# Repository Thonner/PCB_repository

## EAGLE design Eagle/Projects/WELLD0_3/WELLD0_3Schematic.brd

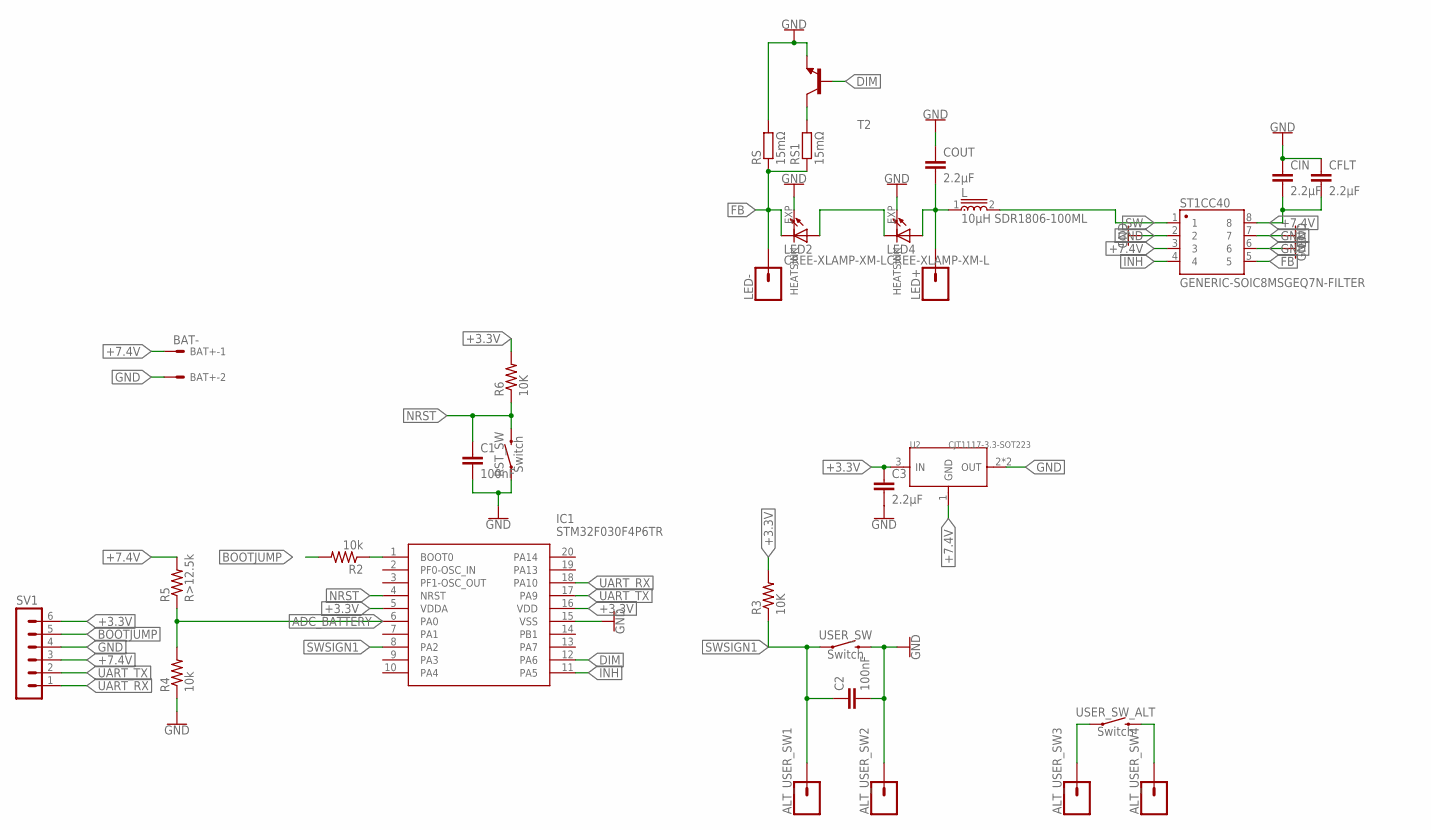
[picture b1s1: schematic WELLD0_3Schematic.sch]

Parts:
ALT_USER_SW1, ALT_USER_SW2, ALT_USER_SW3, ALT_USER_SW4: CONN_01; 1X01
BAT+: BAT-; 6410-02
C1, C2: 100nF; C0603
C3: 2.2µF; C0603
CFLT: 2.2µF; C0603
CIN: 2.2µF; C0603
COUT: 2.2µF; C0603
IC1: STM32F030F4P6TR; SOP65P640X120-20N
L: 10µH SDR1806-100ML; INDP1830X1400X690L250X260N
LED2, LED4: CREE-XLAMP-XM-L
LED+: CONN_01; 1X01
LED-: CONN_01; 1X01
R2, R4: 10k; R0603
R3, R6: 10K; R0603
R5: R>12.5k; R0603
RS, RS1: 15mΩ; M1206
RST_SW: Switch; TACTILE_SWITCH_SMD_6.2MM_TALL
ST1CC40: GENERIC-SOIC8MSGEQ7N-FILTER; SO08
SV1: MA06-1
T2: -NPN-SOT23-BEC; SOT23-BEC
U2: CJT1117-3.3-SOT223; SOT-223
USER_SW: Switch; TACTILE_SWITCH_SMD_6.2MM_TALL
USER_SW_ALT: Switch; TACTILE_SWITCH_SMD_6.2MM_TALL

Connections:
+3.3V: C3.1, IC1.5 (VDDA), IC1.16 (VDD), R3.2, R6.2, SV1.6, U2.3 (IN)
+7.4V: BAT+.1, CFLT.2, CIN.2, R5.2, ST1CC40.3, ST1CC40.8, SV1.3, U2.1 (GND)
ADC_BATTERY: IC1.6 (PA0), R4.2, R5.1
BOOTJUMP: R2.2, SV1.5
DIM: IC1.12 (PA6), T2.B
FB: LED2.C, LED2.C@1 (C), LED-.1, RS.1, RS1.1, ST1CC40.5
GND: ALT_USER_SW2.1, BAT+.2, C1.2, C2.2, C3.2, CFLT.1, CIN.1, COUT.1, IC1.15 (VSS), LED2.EXP (HEATSINK), LED4.EXP (HEATSINK), R4.1, RS.2, RST_SW.A2 (1), ST1CC40.2, ST1CC40.6, ST1CC40.7, SV1.4, T2.E, U2.2 (OUT), U2.TER (OUT), USER_SW.B2 (2)
INH: IC1.11 (PA5), ST1CC40.4
unnamed: COUT.2, L.1, LED4.A, LED4.A@1 (A), LED+.1
unnamed: LED2.A, LED2.A@1 (A), LED4.C, LED4.C@1 (C)
unnamed: RS1.2, T2.C
unnamed: ALT_USER_SW3.1, USER_SW_ALT.A2 (1)
unnamed: ALT_USER_SW4.1, USER_SW_ALT.B2 (2)
unnamed: IC1.1 (BOOT0), R2.1
NRST: C1.1, IC1.4 (NRST), R6.1, RST_SW.B2 (2)
SW: L.2, ST1CC40.1
SWSIGN1: ALT_USER_SW1.1, C2.1, IC1.8 (PA2), R3.1, USER_SW.A2 (1)
UART_RX: IC1.18 (PA10), SV1.1
UART_TX: IC1.17 (PA9), SV1.2

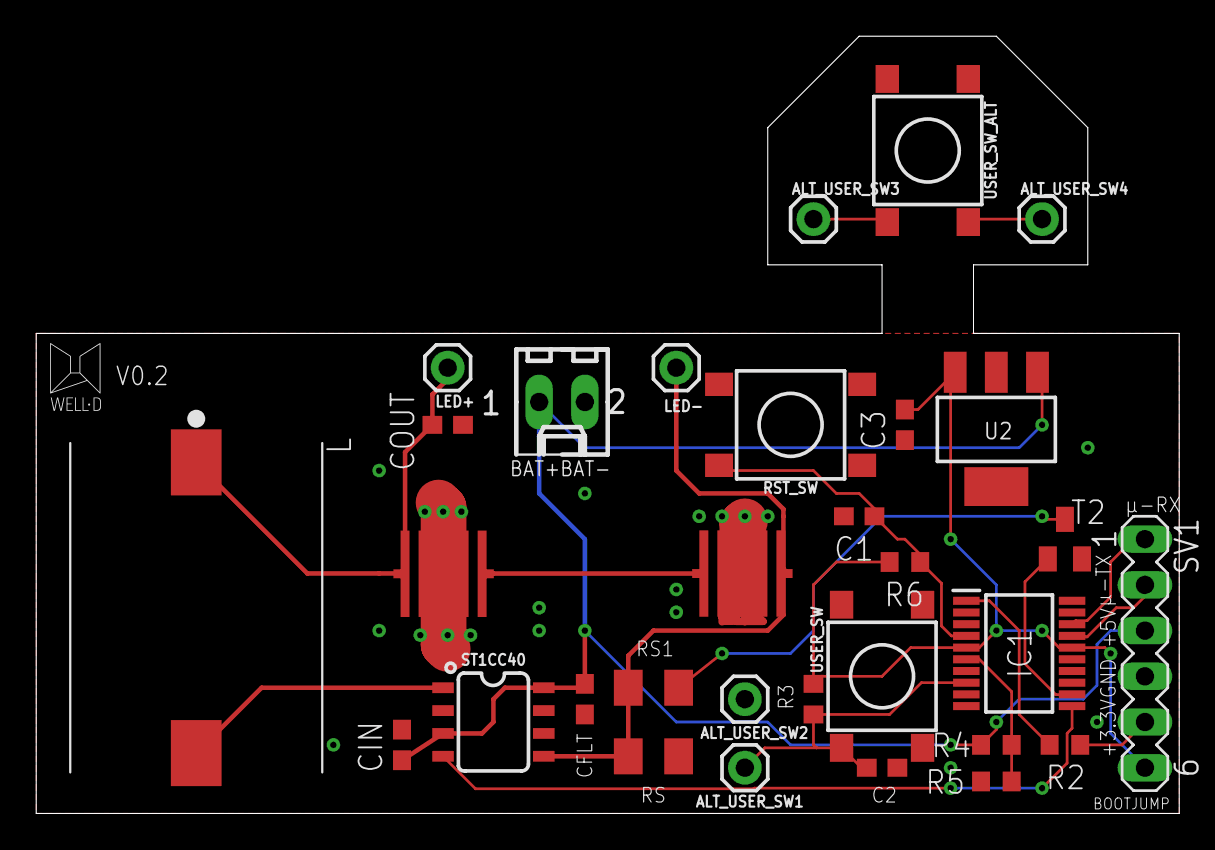
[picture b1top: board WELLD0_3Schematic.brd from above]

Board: 2 copper layers, 63.5 x 43.2 mm, 31 parts (0 on the bottom side), 19 nets.

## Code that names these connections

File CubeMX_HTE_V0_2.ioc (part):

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Mcu.Name=STM32F030F4Px
Mcu.Package=TSSOP20
Mcu.UserName=STM32F030F4Px
PA0.GPIOParameters=GPIO_Label
PA0.GPIO_Label=ADC_battery_mon
PA0.Mode=IN0
PA0.Signal=ADC_IN0
PA10.GPIOParameters=GPIO_Label
PA10.GPIO_Label=UART_RX_PROG
PA10.Mode=Asynchronous
PA10.Signal=USART1_RX
PA2.GPIOParameters=GPIO_PuPd,GPIO_Label
PA2.GPIO_Label=User_Input
PA2.GPIO_PuPd=GPIO_PULLUP
PA2.Signal=GPIO_Input
PA5.GPIOParameters=GPIO_Label
PA5.GPIO_Label=Driver_OnOff_out
PA5.Signal=GPIO_Output
PA6.GPIOParameters=GPIO_Label
PA6.GPIO_Label=DIM_Trans_Out
PA6.Signal=GPIO_Output
PA9.GPIOParameters=GPIO_Label
PA9.GPIO_Label=UART_TX_PROG
PA9.Mode=Asynchronous
PA9.Signal=USART1_TX
board=custom

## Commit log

2018-10-09 Basic component library
2018-10-09 Started eagle project
2018-10-09 More libraries
2018-10-09 Barely started schematic
2018-10-10 Here goes libraries
2018-10-10 LED driver circuit made. (Almost) Have not considered supply, or turn off signal or the dimming mechanism
2018-10-16 Libraries
2018-10-16 Work from 16/10-18
2018-10-24 Circuit done - i guess 24/10-18
2018-10-25 Ready for final thoughts
2018-10-26 Final form - missing heatsink
2018-10-28 Ordered PCB
2018-11-03 Set up cubemx project
2018-11-03 Code for µC has been set up. code for cycling 3 states has been written

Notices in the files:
parts and their libraries:
SparkFun-Connectors: Licensing: Creative Commons ShareAlike 4.0 International - https://creativecommons.org/licenses/by-sa/4.0
